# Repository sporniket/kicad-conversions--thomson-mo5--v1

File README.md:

# Conversion of the Thomson MO5 main board into Kicad

> [WARNING] Please read carefully this note before using this project. It contains important facts.

Content

1. What is **Conversion of the Thomson MO5 main board into Kicad**, and when to use it ?
2. What should you know before using **Conversion of the Thomson MO5 main board into Kicad** ?
3. How to use **Conversion of the Thomson MO5 main board into Kicad** ?
4. Known issues
5. Miscellanous

## 1. What is **Conversion of the Thomson MO5 main board into Kicad**, and when to use it ?

**Conversion of the Thomson MO5 main board into Kicad** is a conversion to Kicad EDA of the schematics of a computer released around 1984 known as the "Thomson MO5".

There are two revisions of the motherboard : 

* The first version, with a Motorola gate array, is maintained on the `main` branch.
* The second version, with an EFCIS gate array, is maintained on the `efcis_gate_array` branch.

### Licence

**Conversion of the Thomson MO5 main board into Kicad** is published under the Creative Commons CC0 license. You can find a copy of the licence there : https://creativecommons.org/publicdomain/zero/1.0/legalcode

You can copy, modify, distribute and perform the work, even for commercial purposes, all without asking permission.

**Conversion of the Thomson MO5 main board into Kicad** is distributed in the hope that it will be useful, but WITHOUT ANY WARRANTY; without even the implied warranty of MERCHANTABILITY or FITNESS FOR A PARTICULAR PURPOSE.

### Release notes

#### v1.0.0-rc2

Because I hastily pushed rc1 and saw small edit just after that : one measurement position, refill the copper pours.

Other than that, same as rc1.

#### v1.0.0-rc1

Fixes found by assembling the motherboard :

* Fixed the power supply : pin 1 of I55 to GND, values of R79 and R80 (shematic is also more easy to understand)
* Fixed the reset circuit : value of C01
* Extended the extension port by 2 mm

For documentation :
* [BOM](README--BOM.md)
* Added measurements to the PCB.

#### v1.0.0-beta-2

* Issue #1 -- Small corrections for beta2
  * Schematic -- fixes unit of L01, 'nH' instead of 'mH'
  * wider lateral chamfers for extension connector, set to 1mm along x and y axis
  * prevent a small copper pour of GND inside the extension connector
  * exclude copper pour around internal mounting holes (front layer)
  * tweak the width of the pads of the extension connector, from 2mm to 1.5mm

* Issue #2 -- Small enhancements for beta2
  * Silkscreen -- add text to render REVISION and ISSUE_DATE
  * enlarge vias for modding cartridge port to get E and R/W 
  * Some additionnal fixes of DRC violations
  * Schematic -- D02 value becomes 'BZX46C12'
  * Reset switch -- ad-hoc footprint to combine regular switch with the original reset button footprint

#### v1.0.0-beta-1

The PCB is finished, ready for testing (mechanical, actual assembly) to spot errors.

#### v1.0.0-alpha-1 to v1.0.0-alpha-6

The whole schematics has been captured, need proofreading. A new alpha is produced regularly after some fixes are commited.

## 2. What should you know before using **Conversion of the Thomson MO5 main board into Kicad** ?

**Conversion of the Thomson MO5 main board into Kicad** is made using Kicad 7.

> Do not use **Conversion of the Thomson MO5 main board into Kicad** if this project is not suitable for your project.

## 3. How to use **Conversion of the Thomson MO5 main board into Kicad** ?

### From sources

To get the latest available work, one must clone the git repository.

	git clone --recurse-submodules https://github.com/sporniket/kicad-conversions--thomson-mo5--v1.git

Then, open the project with Kicad 7.

## 4. Known issues
See the [project issues](https://github.com/sporniket/kicad-conversions--thomson-mo5--v1/issues) page.

## 5. Miscellanous

### Report issues
Use the [project issues](https://github.com/sporniket/kicad-conversions--thomson-mo5--v1/issues) page.

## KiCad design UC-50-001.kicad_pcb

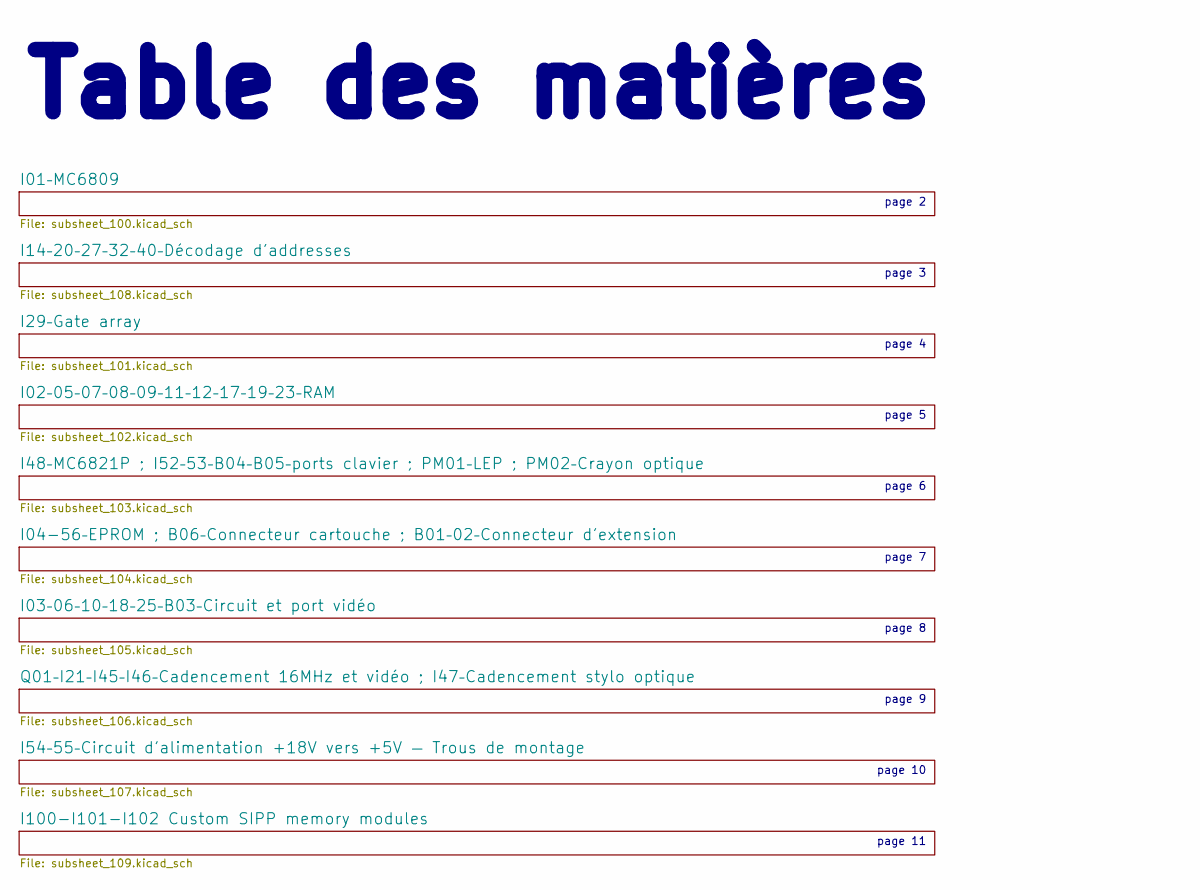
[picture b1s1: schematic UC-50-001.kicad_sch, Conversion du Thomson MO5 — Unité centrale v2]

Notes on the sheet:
page 10
page 2
page 11
page 4
page 6
page 9
page 7
Table des matières
page 5
page 8
page 3

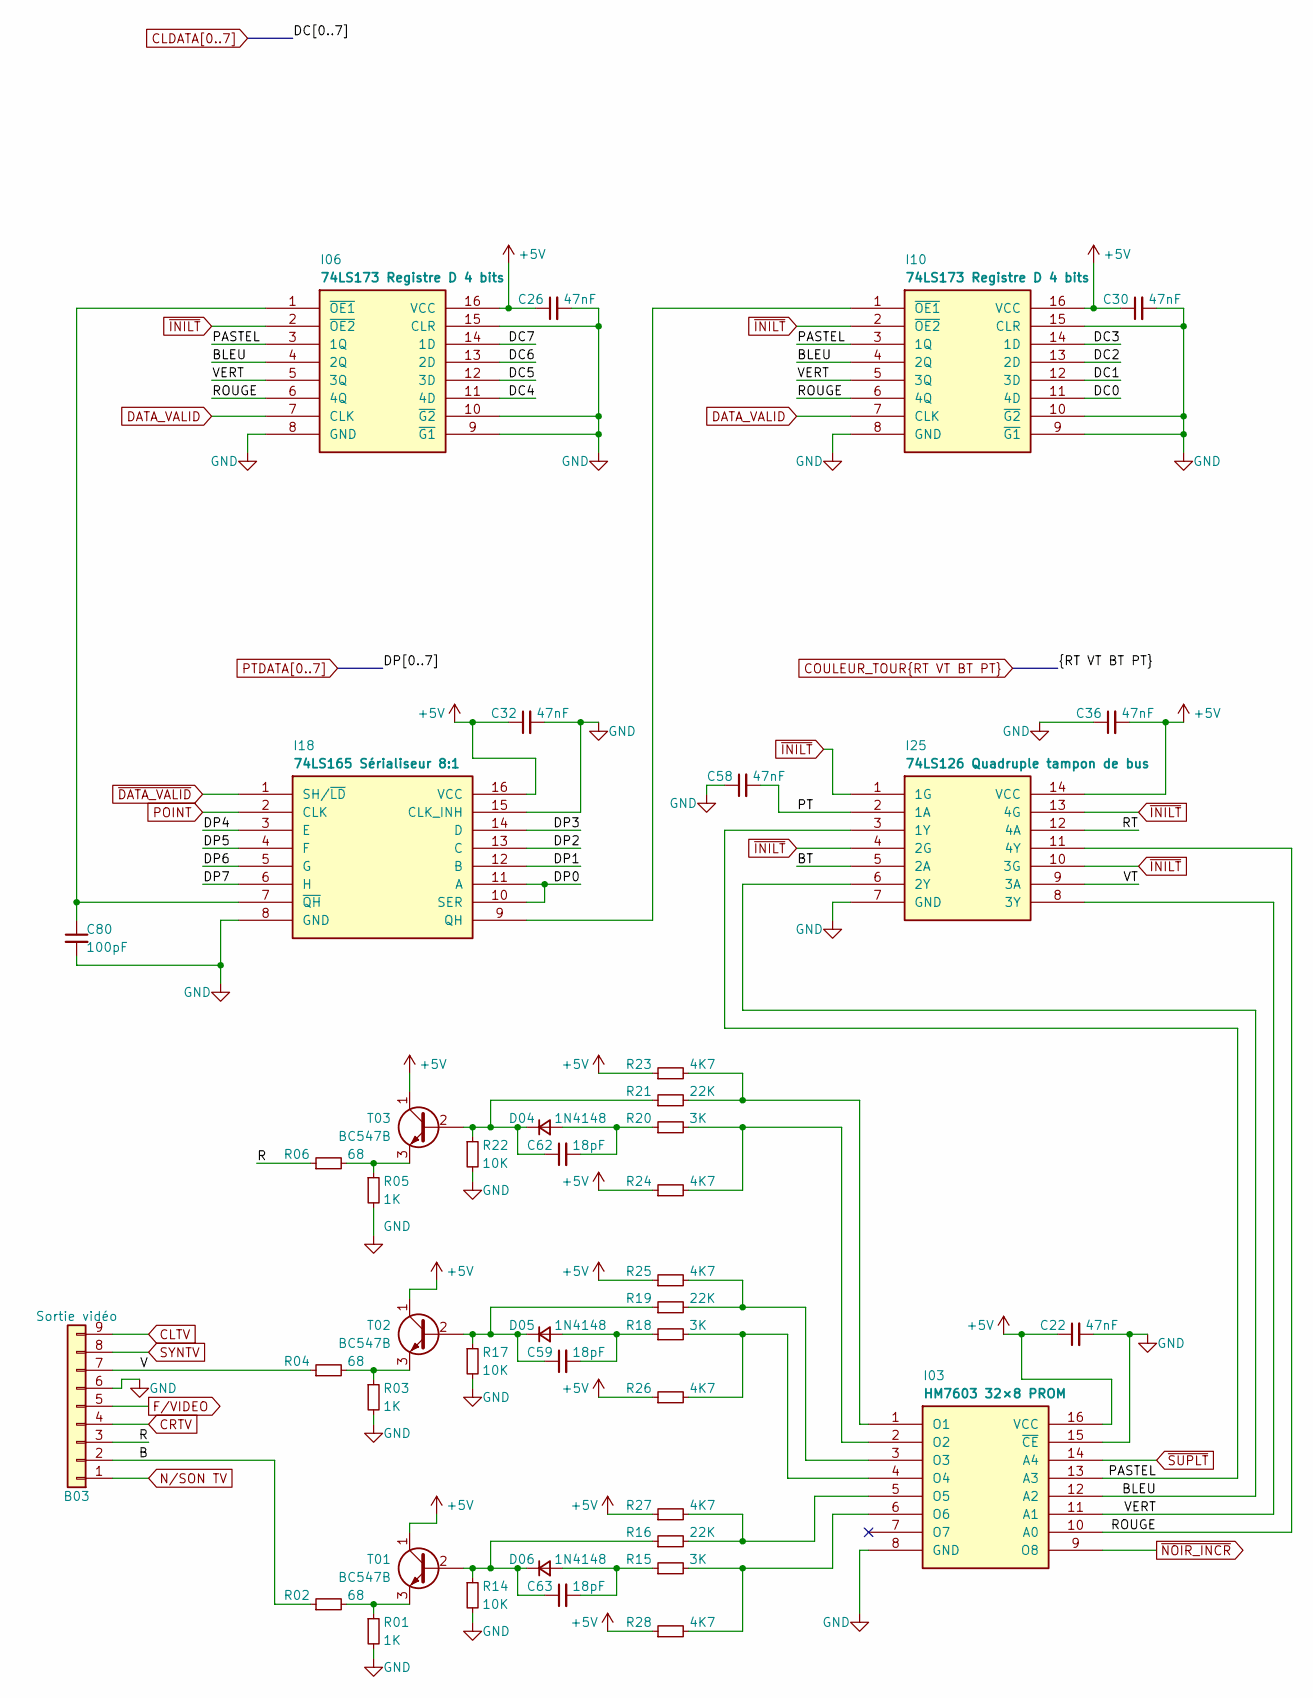
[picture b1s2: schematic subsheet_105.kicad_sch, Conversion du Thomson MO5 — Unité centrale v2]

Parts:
B03: Sortie vidéo; Keyed_MaleReceptacle_1x09_P2.54mm_THT_Vertical
C22, C26, C30, C32, C36, C58: 47nF; Passive_THT_capacitor_mlcc_W2.54mm_L5.08mm
C59, C62, C63: 18pF; Passive_THT_capacitor_mlcc_W2.54mm_L5.08mm
C80: 100pF; Passive_THT_capacitor_mlcc_W2.54mm_L5.08mm
D04, D05, D06: 1N4148; Passive_THT_diode_W2.54mm_L12.70mm
I03: HM7603 32×8 PROM; DIP-16_W7.62mm_LongPads
I06, I10: 74LS173 Registre D 4 bits; DIP-16_W7.62mm_LongPads
I18: 74LS165 Sérialiseur 8:1; DIP-16_W7.62mm_LongPads
I25: 74LS126 Quadruple tampon de bus; DIP-14_W7.62mm_LongPads
R01, R03, R05: 1K; Passive_THT_resistor_EU_W2.54mm_L12.70mm
R02, R04, R06: 68; Passive_THT_resistor_EU_W2.54mm_L12.70mm
R14, R17, R22: 10K; Passive_THT_resistor_EU_W2.54mm_L12.70mm
R15, R18, R20: 3K; Passive_THT_resistor_EU_W2.54mm_L12.70mm
R16, R19, R21: 22K; Passive_THT_resistor_EU_W2.54mm_L12.70mm
R23, R24, R25, R26, R27, R28: 4K7; Passive_THT_resistor_EU_W2.54mm_L12.70mm
T01, T02, T03: BC547B; TO-92_Inline_Wide

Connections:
+5V: C22.1, C26.1, C30.1, C32.1, C36.2, I03.16 (VCC), I06.16 (VCC), I10.16 (VCC), I18.16 (VCC), I25.14 (VCC), R23.1, R24.1, R25.1, R26.1, R27.1, R28.1, T01.1 (C), T02.1 (C), T03.1 (C); also elsewhere on the board
/I03–06–10–18–25–B03–Circuit et port vidéo /B: B03.2, R02.1
/I03–06–10–18–25–B03–Circuit et port vidéo /BLEU: I03.12 (A2), I06.4 (2Q), I10.4 (2Q), I25.6 (2Y)
/I03–06–10–18–25–B03–Circuit et port vidéo /PASTEL: I03.13 (A3), I06.3 (1Q), I10.3 (1Q), I25.3 (1Y)
/I03–06–10–18–25–B03–Circuit et port vidéo /R: B03.3, R06.1
/I03–06–10–18–25–B03–Circuit et port vidéo /ROUGE: I03.10 (A0), I06.6 (4Q), I10.6 (4Q), I25.11 (4Y)
/I03–06–10–18–25–B03–Circuit et port vidéo /V: B03.7, R04.1
/I03–06–10–18–25–B03–Circuit et port vidéo /VERT: I03.11 (A1), I06.5 (3Q), I10.5 (3Q), I25.8 (3Y)
CLDATA0: I10.11 (4D); also elsewhere on the board
CLDATA1: I10.12 (3D); also elsewhere on the board
CLDATA2: I10.13 (2D); also elsewhere on the board
CLDATA3: I10.14 (1D); also elsewhere on the board
CLDATA4: I06.11 (4D); also elsewhere on the board
CLDATA5: I06.12 (3D); also elsewhere on the board
CLDATA6: I06.13 (2D); also elsewhere on the board
CLDATA7: I06.14 (1D); also elsewhere on the board
CLTV: B03.9; also elsewhere on the board
COULEUR_TOUR.BT: I25.5 (2A); also elsewhere on the board
COULEUR_TOUR.PT: C58.2, I25.2 (1A); also elsewhere on the board
COULEUR_TOUR.RT: I25.12 (4A); also elsewhere on the board
COULEUR_TOUR.VT: I25.9 (3A); also elsewhere on the board
CRTV: B03.4; also elsewhere on the board
DATA_VALID: I06.7 (CLK), I10.7 (CLK); also elsewhere on the board
F/VIDEO: B03.5; also elsewhere on the board
GND: B03.6, C22.2, C26.2, C30.2, C32.2, C36.1, C58.1, C80.2, I03.8 (GND), I03.15 (~CE), I06.8 (GND), I06.9 (~G1), I06.10 (~G2), I06.15 (CLR), I10.8 (GND), I10.9 (~G1), I10.10 (~G2), I10.15 (CLR), I18.8 (GND), I18.15 (CLK_INH), I25.7 (GND), R01.2, R03.2, R05.2, R14.2, R17.2, R22.2; also elsewhere on the board
unnamed: C62.2, D04.2 (A), R20.1
unnamed: C62.1, D04.1 (K), R21.1, R22.1, T03.2 (B)
unnamed: C59.2, D05.2 (A), R18.1
unnamed: C59.1, D05.1 (K), R17.1, R19.1, T02.2 (B)
unnamed: C63.2, D06.2 (A), R15.1
unnamed: C63.1, D06.1 (K), R14.1, R16.1, T01.2 (B)
unnamed: I03.1 (O1), R21.2, R23.2
unnamed: I03.2 (O2), R20.2, R24.2
unnamed: I03.3 (O3), R19.2, R25.2
unnamed: I03.4 (O4), R18.2, R26.2
unnamed: I03.5 (O5), R16.2, R27.2
unnamed: I03.6 (O6), R15.2, R28.2
unnamed: C80.1, I06.1 (~OE1), I18.7 (~QH)
unnamed: I10.1 (~OE1), I18.9 (QH)
unnamed: R01.1, R02.2, T01.3 (E)
unnamed: R03.1, R04.2, T02.3 (E)
unnamed: R05.1, R06.2, T03.3 (E)
N/SON TV: B03.1; also elsewhere on the board
POINT: I18.2 (CLK); also elsewhere on the board
PTDATA0: I18.10 (SER), I18.11 (A); also elsewhere on the board
PTDATA1: I18.12 (B); also elsewhere on the board
PTDATA2: I18.13 (C); also elsewhere on the board
PTDATA3: I18.14 (D); also elsewhere on the board
PTDATA4: I18.3 (E); also elsewhere on the board
PTDATA5: I18.4 (F); also elsewhere on the board
PTDATA6: I18.5 (G); also elsewhere on the board
PTDATA7: I18.6 (H); also elsewhere on the board
SYNTV: B03.8; also elsewhere on the board
~DATA_VALID: I18.1 (SH/~LD); also elsewhere on the board
~INILT: I06.2 (~OE2), I10.2 (~OE2), I25.1 (1G), I25.4 (2G), I25.10 (3G), I25.13 (4G); also elsewhere on the board
~NOIR_INCR: I03.9 (O8); also elsewhere on the board
~SUPLT: I03.14 (A4); also elsewhere on the board

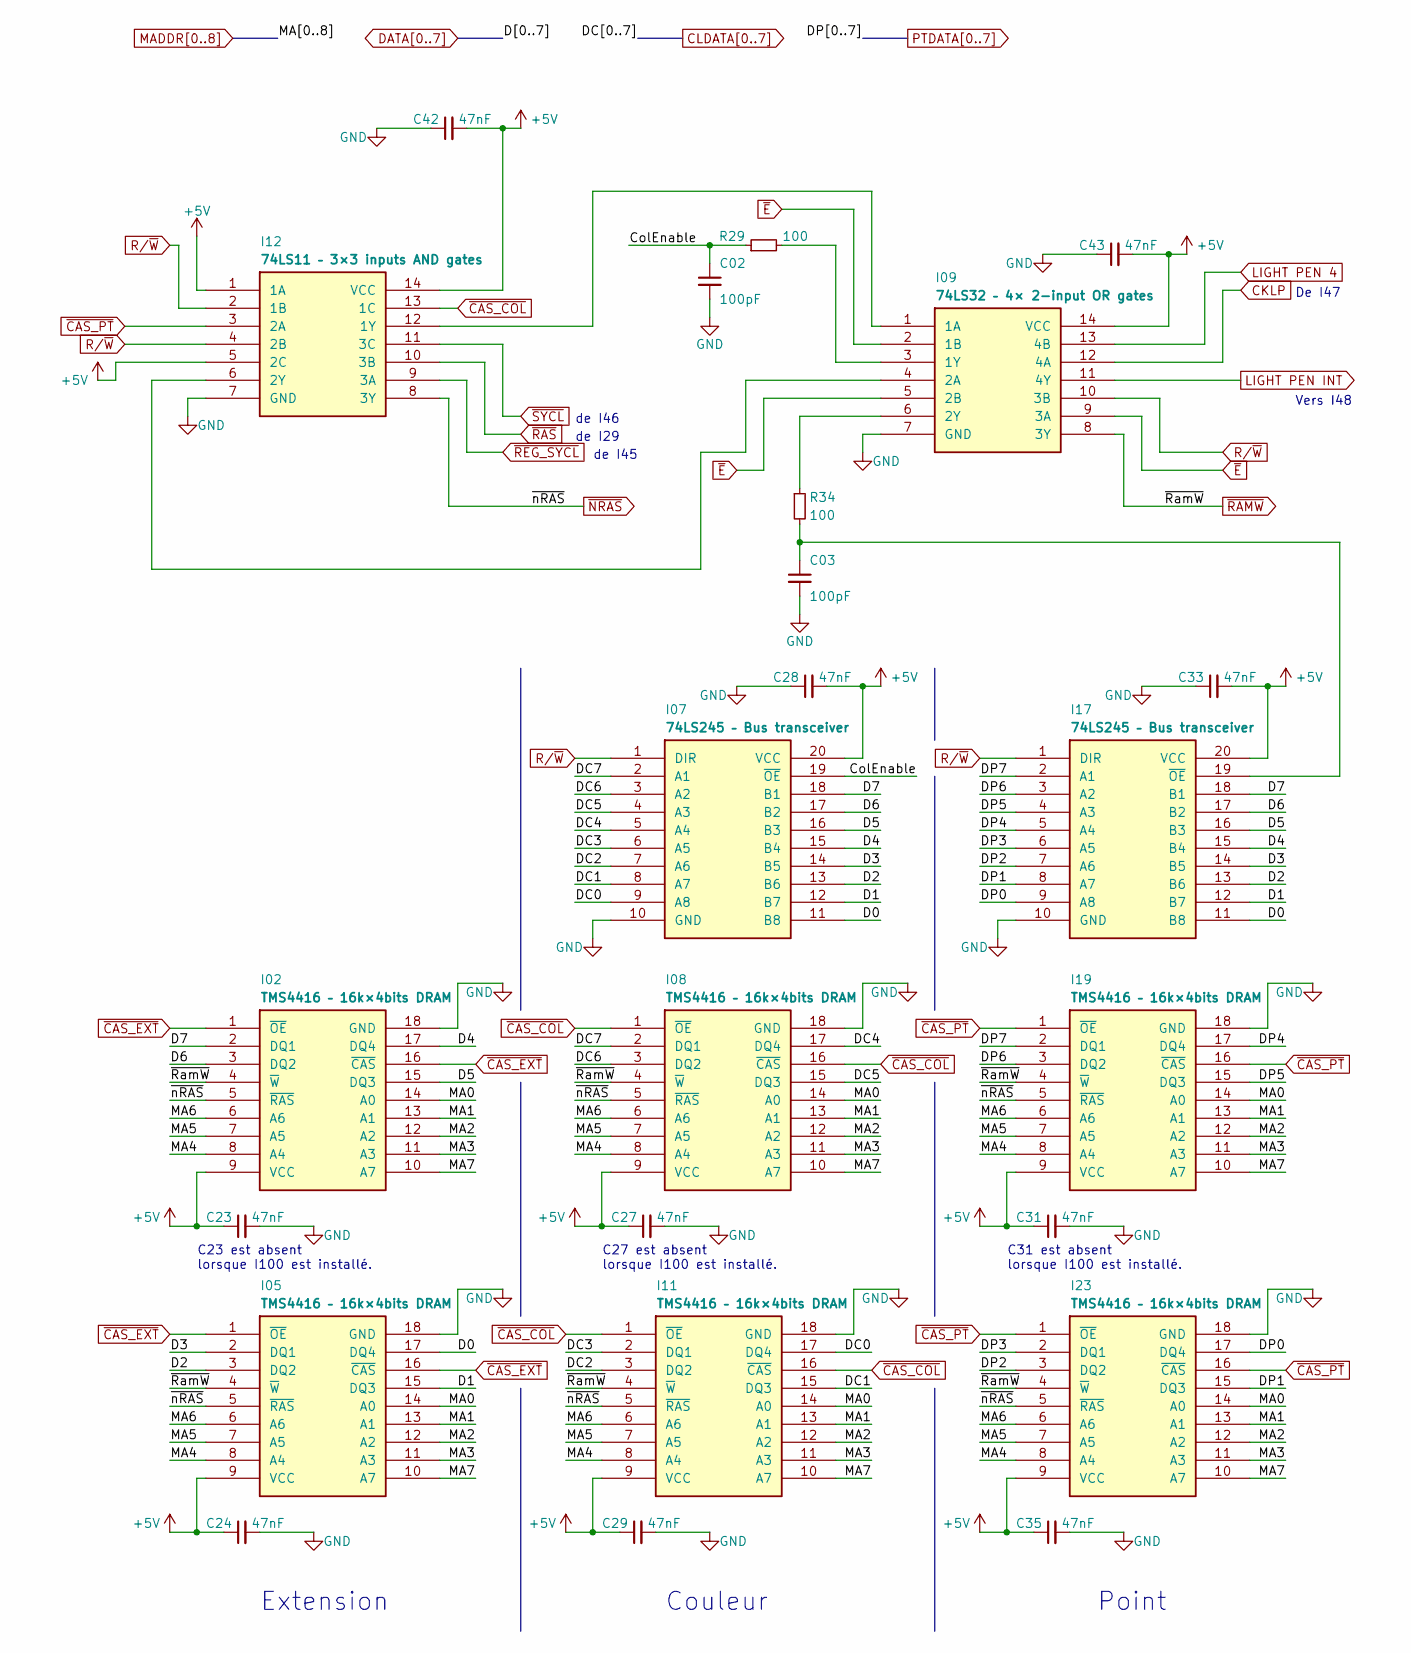
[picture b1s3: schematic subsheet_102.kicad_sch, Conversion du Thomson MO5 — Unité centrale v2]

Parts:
C02, C03: 100pF; Passive_THT_capacitor_mlcc_W2.54mm_L5.08mm
C23, C24, C27, C28, C29, C31, C33, C35, C42, C43: 47nF; Passive_THT_capacitor_mlcc_W2.54mm_L5.08mm
I02, I05, I08, I11, I19, I23: TMS4416 – 16k×4bits DRAM; DIP-18_W7.62mm_LongPads
I07, I17: 74LS245 – Bus transceiver; DIP-20_W7.62mm_LongPads
I09: 74LS32 – 4× 2-input OR gates; DIP-14_W7.62mm_LongPads
I12: 74LS11 – 3×3 inputs AND gates; DIP-14_W7.62mm_LongPads
R29, R34: 100; Passive_THT_resistor_EU_W2.54mm_L12.70mm

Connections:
+5V: C23.1, C24.1, C27.1, C28.2, C29.1, C31.1, C33.2, C35.1, C42.2, C43.2, I02.9 (VCC), I05.9 (VCC), I07.20 (VCC), I08.9 (VCC), I09.14 (VCC), I11.9 (VCC), I12.1 (1A), I12.5 (2C), I12.14 (VCC), I17.20 (VCC), I19.9 (VCC), I23.9 (VCC); also elsewhere on the board
/I02–05–07–08–09–11–12–17–19–23–RAM/ColEnable: C02.1, I07.19 (~OE), R29.1
CKLP: I09.12 (4A); also elsewhere on the board
CLDATA0: I07.9 (A8), I11.17 (DQ4); also elsewhere on the board
CLDATA1: I07.8 (A7), I11.15 (DQ3); also elsewhere on the board
CLDATA2: I07.7 (A6), I11.3 (DQ2); also elsewhere on the board
CLDATA3: I07.6 (A5), I11.2 (DQ1); also elsewhere on the board
CLDATA4: I07.5 (A4), I08.17 (DQ4); also elsewhere on the board
CLDATA5: I07.4 (A3), I08.15 (DQ3); also elsewhere on the board
CLDATA6: I07.3 (A2), I08.3 (DQ2); also elsewhere on the board
CLDATA7: I07.2 (A1), I08.2 (DQ1); also elsewhere on the board
DATA0: I05.17 (DQ4), I07.11 (B8), I17.11 (B8); also elsewhere on the board
DATA1: I05.15 (DQ3), I07.12 (B7), I17.12 (B7); also elsewhere on the board
DATA2: I05.3 (DQ2), I07.13 (B6), I17.13 (B6); also elsewhere on the board
DATA3: I05.2 (DQ1), I07.14 (B5), I17.14 (B5); also elsewhere on the board
DATA4: I02.17 (DQ4), I07.15 (B4), I17.15 (B4); also elsewhere on the board
DATA5: I02.15 (DQ3), I07.16 (B3), I17.16 (B3); also elsewhere on the board
DATA6: I02.3 (DQ2), I07.17 (B2), I17.17 (B2); also elsewhere on the board
DATA7: I02.2 (DQ1), I07.18 (B1), I17.18 (B1); also elsewhere on the board
GND: C02.2, C03.2, C23.2, C24.2, C27.2, C28.1, C29.2, C31.2, C33.1, C35.2, C42.1, C43.1, I02.18 (GND), I05.18 (GND), I07.10 (GND), I08.18 (GND), I09.7 (GND), I11.18 (GND), I12.7 (GND), I17.10 (GND), I19.18 (GND), I23.18 (GND); also elsewhere on the board
LIGHT PEN 4: I09.13 (4B); also elsewhere on the board
LIGHT PEN INT: I09.11 (4Y); also elsewhere on the board
MADDR0: I02.14 (A0), I05.14 (A0), I08.14 (A0), I11.14 (A0), I19.14 (A0), I23.14 (A0); also elsewhere on the board
MADDR1: I02.13 (A1), I05.13 (A1), I08.13 (A1), I11.13 (A1), I19.13 (A1), I23.13 (A1); also elsewhere on the board
MADDR2: I02.12 (A2), I05.12 (A2), I08.12 (A2), I11.12 (A2), I19.12 (A2), I23.12 (A2); also elsewhere on the board
MADDR3: I02.11 (A3), I05.11 (A3), I08.11 (A3), I11.11 (A3), I19.11 (A3), I23.11 (A3); also elsewhere on the board
MADDR4: I02.8 (A4), I05.8 (A4), I08.8 (A4), I11.8 (A4), I19.8 (A4), I23.8 (A4); also elsewhere on the board
MADDR5: I02.7 (A5), I05.7 (A5), I08.7 (A5), I11.7 (A5), I19.7 (A5), I23.7 (A5); also elsewhere on the board
MADDR6: I02.6 (A6), I05.6 (A6), I08.6 (A6), I11.6 (A6), I19.6 (A6), I23.6 (A6); also elsewhere on the board
MADDR7: I02.10 (A7), I05.10 (A7), I08.10 (A7), I11.10 (A7), I19.10 (A7), I23.10 (A7); also elsewhere on the board
unnamed: I09.1 (1A), I12.12 (1Y)
unnamed: I09.3 (1Y), R29.2
unnamed: I09.4 (2A), I12.6 (2Y)
unnamed: I09.6 (2Y), R34.1
unnamed: C03.1, I17.19 (~OE), R34.2
PTDATA0: I17.9 (A8), I23.17 (DQ4); also elsewhere on the board
PTDATA1: I17.8 (A7), I23.15 (DQ3); also elsewhere on the board
PTDATA2: I17.7 (A6), I23.3 (DQ2); also elsewhere on the board
PTDATA3: I17.6 (A5), I23.2 (DQ1); also elsewhere on the board
PTDATA4: I17.5 (A4), I19.17 (DQ4); also elsewhere on the board
PTDATA5: I17.4 (A3), I19.15 (DQ3); also elsewhere on the board
PTDATA6: I17.3 (A2), I19.3 (DQ2); also elsewhere on the board
PTDATA7: I17.2 (A1), I19.2 (DQ1); also elsewhere on the board
R/~W: I07.1 (DIR), I09.10 (3B), I12.2 (1B), I12.4 (2B), I17.1 (DIR); also elsewhere on the board
~CAS_COL: I08.1 (~OE), I08.16 (~CAS), I11.1 (~OE), I11.16 (~CAS), I12.13 (1C); also elsewhere on the board
~CAS_EXT: I02.1 (~OE), I02.16 (~CAS), I05.1 (~OE), I05.16 (~CAS); also elsewhere on the board
~CAS_PT: I12.3 (2A), I19.1 (~OE), I19.16 (~CAS), I23.1 (~OE), I23.16 (~CAS); also elsewhere on the board
~E: I09.2 (1B), I09.5 (2B), I09.9 (3A); also elsewhere on the board
~NRAS: I02.5 (~RAS), I05.5 (~RAS), I08.5 (~RAS), I11.5 (~RAS), I12.8 (3Y), I19.5 (~RAS), I23.5 (~RAS); also elsewhere on the board
~RAMW: I02.4 (~W), I05.4 (~W), I08.4 (~W), I09.8 (3Y), I11.4 (~W), I19.4 (~W), I23.4 (~W); also elsewhere on the board
~RAS: I12.10 (3B); also elsewhere on the board
~REG_SYCL: I12.9 (3A); also elsewhere on the board
~SYCL: I12.11 (3C); also elsewhere on the board

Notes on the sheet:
C31 est absent lorsque I100 est installé.
de I29
Extension
Vers I48
C27 est absent lorsque I100 est installé.
de I45
C23 est absent lorsque I100 est installé.
De I47
Couleur
de I46
Point

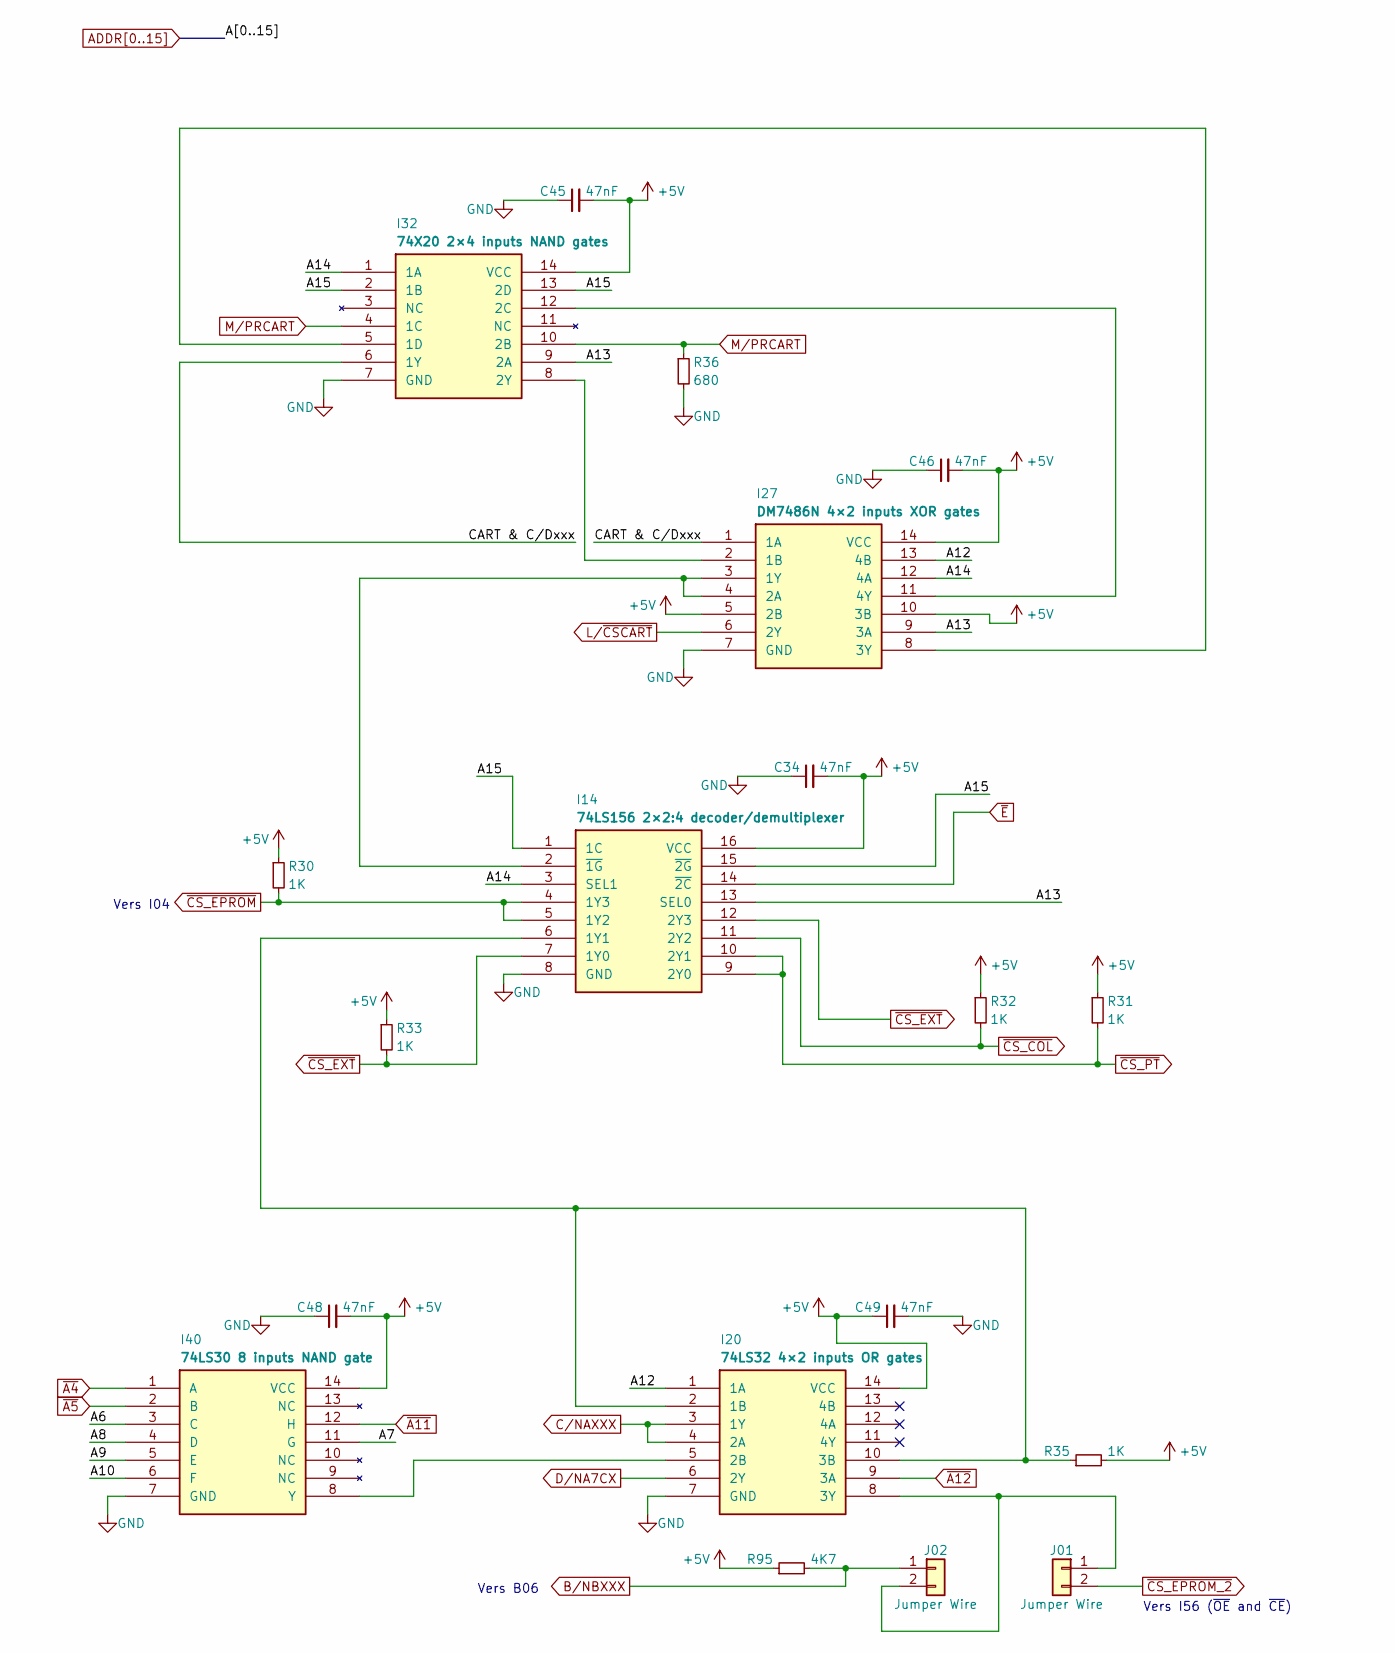
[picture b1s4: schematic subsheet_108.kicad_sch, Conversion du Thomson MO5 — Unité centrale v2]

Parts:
C34, C45, C46, C48, C49: 47nF; Passive_THT_capacitor_mlcc_W2.54mm_L5.08mm
I14: 74LS156 2×2:4 decoder/demultiplexer; DIP-16_W7.62mm_LongPads
I20: 74LS32 4×2 inputs OR gates; DIP-14_W7.62mm_LongPads
I27: DM7486N 4×2 inputs XOR gates; DIP-14_W7.62mm_LongPads
I32: 74X20 2×4 inputs NAND gates; DIP-14_W7.62mm_LongPads
I40: 74LS30 8 inputs NAND gate; DIP-14_W7.62mm_LongPads
J01, J02: Jumper Wire; Passive_THT_jumper_wire_W2.54mm_L10.16mm
R30, R31, R32, R33, R35: 1K; Passive_THT_resistor_EU_W2.54mm_L12.70mm
R36: 680; Passive_THT_resistor_EU_W2.54mm_L12.70mm
R95: 4K7; Passive_THT_resistor_EU_W2.54mm_L12.70mm

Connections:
+5V: C34.2, C45.2, C46.2, C48.2, C49.1, I14.16 (VCC), I20.14 (VCC), I27.5 (2B), I27.10 (3B), I27.14 (VCC), I32.14 (VCC), I40.14 (VCC), R30.1, R31.1, R32.1, R33.1, R35.2, R95.1; also elsewhere on the board
/I14–20–27–32–40–Décodage d'addresses/CART & C/Dxxx: I27.1 (1A), I32.6 (1Y)
ADDR6: I40.3 (C); also elsewhere on the board
ADDR7: I40.11 (G); also elsewhere on the board
ADDR8: I40.4 (D); also elsewhere on the board
ADDR9: I40.5 (E); also elsewhere on the board
ADDR10: I40.6 (F); also elsewhere on the board
ADDR12: I20.1 (1A), I27.13 (4B); also elsewhere on the board
ADDR13: I14.13 (SEL0), I27.9 (3A), I32.9 (2A); also elsewhere on the board
ADDR14: I14.3 (SEL1), I27.12 (4A), I32.1 (1A); also elsewhere on the board
ADDR15: I14.1 (1C), I14.15 (~2G), I32.2 (1B), I32.13 (2D); also elsewhere on the board
B/NBXXX: J02.1, R95.2; also elsewhere on the board
C/NAXXX: I20.3 (1Y), I20.4 (2A); also elsewhere on the board
D/NA7CX: I20.6 (2Y); also elsewhere on the board
GND: C34.1, C45.1, C46.1, C48.1, C49.2, I14.8 (GND), I20.7 (GND), I27.7 (GND), I32.7 (GND), I40.7 (GND), R36.2; also elsewhere on the board
L/~CSCART: I27.6 (2Y); also elsewhere on the board
M/PRCART: I32.4 (1C), I32.10 (2B), R36.1; also elsewhere on the board
unnamed: I14.6 (1Y1), I20.2 (1B), I20.10 (3B), R35.1
unnamed: I14.2 (~1G), I27.3 (1Y), I27.4 (2A)
unnamed: I20.5 (2B), I40.8 (Y)
unnamed: I20.8 (3Y), J01.1, J02.2
unnamed: I27.2 (1B), I32.8 (2Y)
unnamed: I27.8 (3Y), I32.5 (1D)
unnamed: I27.11 (4Y), I32.12 (2C)
~A4: I40.1 (A); also elsewhere on the board
~A5: I40.2 (B); also elsewhere on the board
~A11: I40.12 (H); also elsewhere on the board
~A12: I20.9 (3A); also elsewhere on the board
~CS_COL: I14.11 (2Y2), R32.2; also elsewhere on the board
~CS_EPROM_2: J01.2; also elsewhere on the board
~CS_EPROM: I14.4 (1Y3), I14.5 (1Y2), R30.2; also elsewhere on the board
~CS_EXT: I14.7 (1Y0), I14.12 (2Y3), R33.2; also elsewhere on the board
~CS_PT: I14.9 (2Y0), I14.10 (2Y1), R31.2; also elsewhere on the board
~E: I14.14 (~2C); also elsewhere on the board

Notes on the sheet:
Vers I56 (~{OE} and ~{CE})
Vers B06
Vers I04

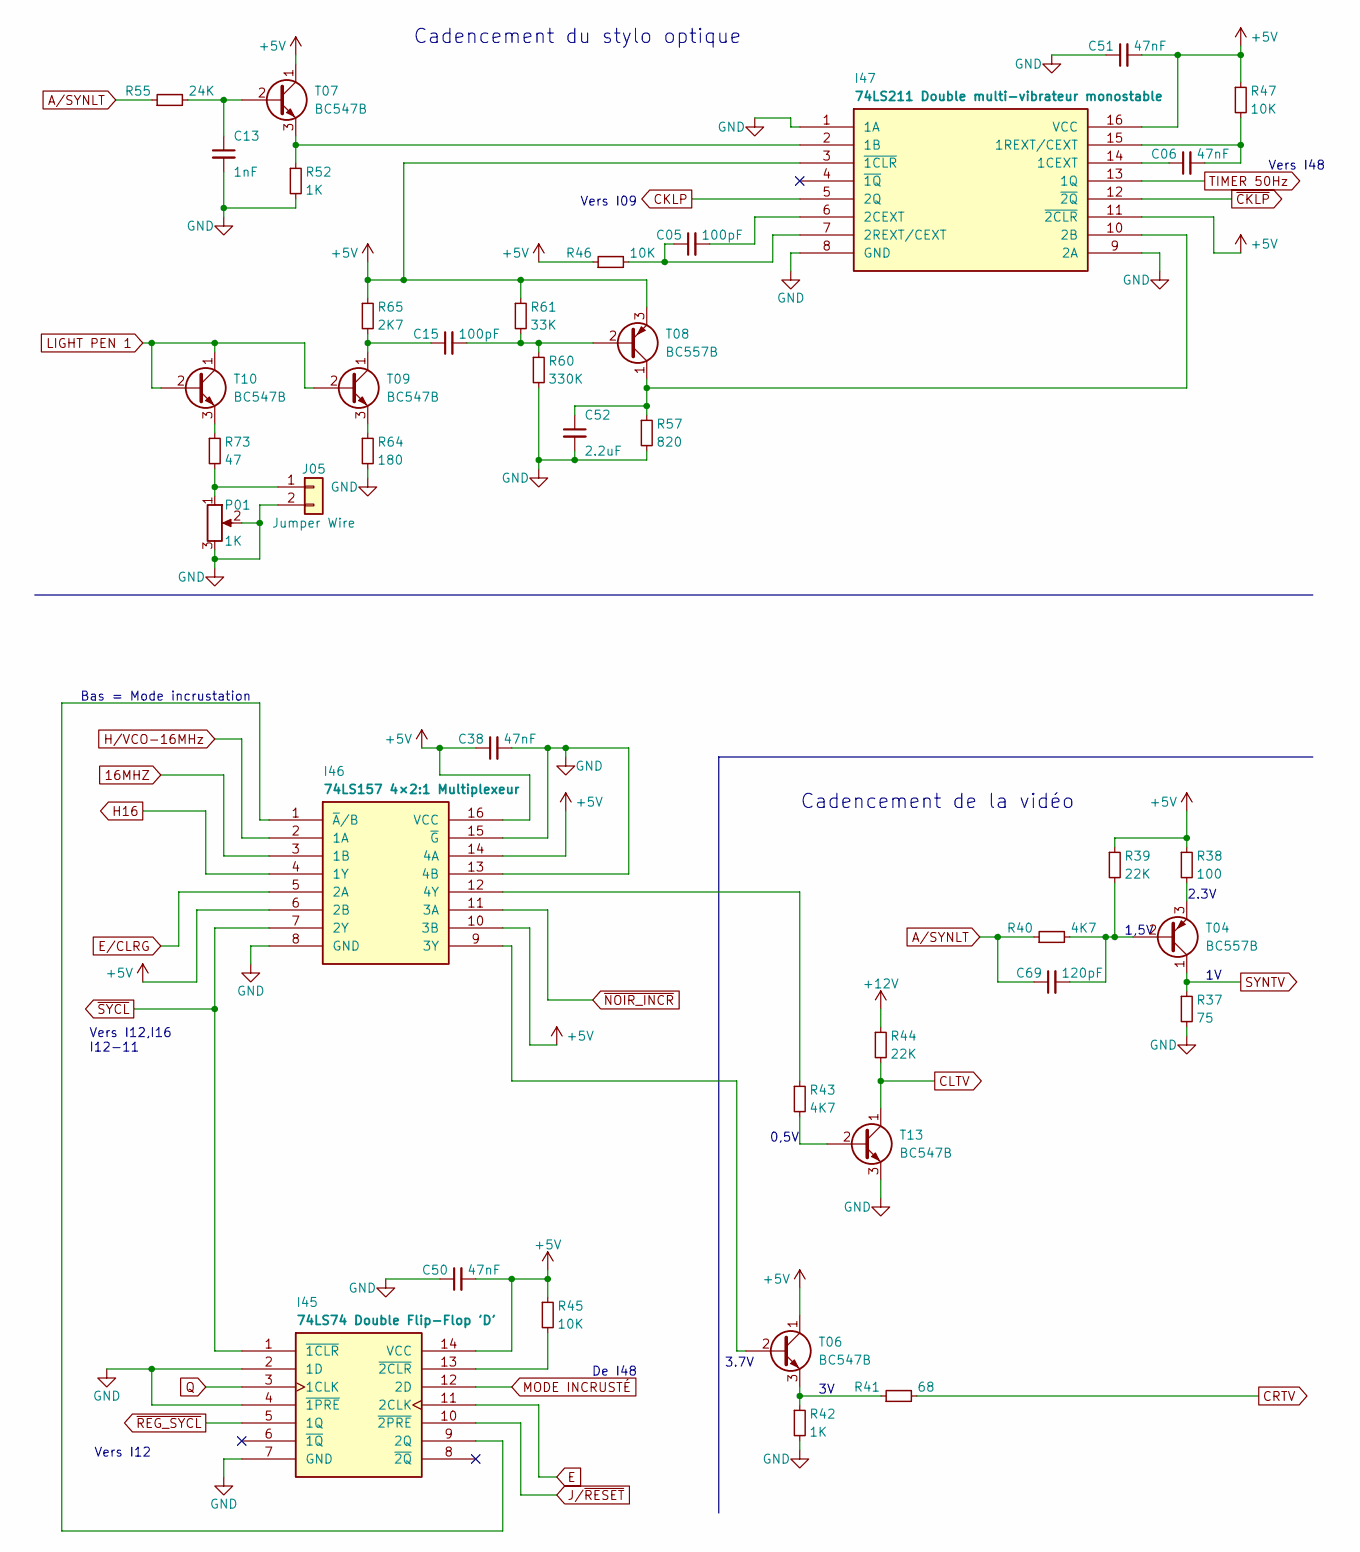
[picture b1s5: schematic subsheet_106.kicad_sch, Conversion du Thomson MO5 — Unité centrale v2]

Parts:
C05, C15: 100pF; Passive_THT_capacitor_mlcc_W2.54mm_L5.08mm
C06, C38, C50, C51: 47nF; Passive_THT_capacitor_mlcc_W2.54mm_L5.08mm
C13: 1nF; Passive_THT_capacitor_mlcc_W2.54mm_L5.08mm
C52: 2.2uF; Passive_THT_capacitor_mlcc_W2.54mm_L5.08mm
C69: 120pF; Passive_THT_capacitor_mlcc_W2.54mm_L5.08mm
I45: 74LS74 Double Flip-Flop 'D'; DIP-14_W7.62mm_LongPads
I46: 74LS157 4×2:1 Multiplexeur; DIP-16_W7.62mm_LongPads
I47: 74LS211 Double multi-vibrateur monostable; DIP-16_W7.62mm_LongPads
J05: Jumper Wire; Passive_THT_jumper_wire_W2.54mm_L12.70mm
P01: 1K; Potentiometer_ACP_CA9-V10_Vertical_Hole
R37: 75; Passive_THT_resistor_EU_W2.54mm_L12.70mm
R38: 100; Passive_THT_resistor_EU_W2.54mm_L12.70mm
R39, R44: 22K; Passive_THT_resistor_EU_W2.54mm_L12.70mm
R40, R43: 4K7; Passive_THT_resistor_EU_W2.54mm_L12.70mm
R41: 68; Passive_THT_resistor_EU_W2.54mm_L12.70mm
R42, R52: 1K; Passive_THT_resistor_EU_W2.54mm_L12.70mm
R45, R46, R47: 10K; Passive_THT_resistor_EU_W2.54mm_L12.70mm
R55: 24K; Passive_THT_resistor_EU_W2.54mm_L12.70mm
R57: 820; Passive_THT_resistor_EU_W2.54mm_L12.70mm
R60: 330K; Passive_THT_resistor_EU_W2.54mm_L12.70mm
R61: 33K; Passive_THT_resistor_EU_W2.54mm_L12.70mm
R64: 180; Passive_THT_resistor_EU_W2.54mm_L12.70mm
R65: 2K7; Passive_THT_resistor_EU_W2.54mm_L12.70mm
R73: 47; Passive_THT_resistor_EU_W2.54mm_L12.70mm
T04, T08: BC557B; TO-92_Inline_Wide
T06, T07, T09, T10, T13: BC547B; TO-92_Inline_Wide

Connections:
16MHZ: I46.3 (1B); also elsewhere on the board
+5V: C38.1, C50.2, C51.2, I45.14 (VCC), I46.6 (2B), I46.10 (3B), I46.14 (4A), I46.16 (VCC), I47.3 (~1CLR), I47.11 (~2CLR), I47.16 (VCC), R38.1, R39.1, R45.1, R46.1, R47.1, R61.1, R65.1, T06.1 (C), T07.1 (C), T08.3 (E); also elsewhere on the board
+12V: R44.1; also elsewhere on the board
A/SYNLT: C69.1, R40.1, R55.1; also elsewhere on the board
CKLP: I47.5 (2Q); also elsewhere on the board
CLTV: R44.2, T13.1 (C); also elsewhere on the board
CRTV: R41.2; also elsewhere on the board
E: I45.11 (2CLK); also elsewhere on the board
E/CLRG: I46.5 (2A); also elsewhere on the board
GND: C13.2, C38.2, C50.1, C51.1, C52.2, I45.2 (1D), I45.4 (~1PRE), I45.7 (GND), I46.8 (GND), I46.13 (4B), I46.15 (~G), I47.1 (1A), I47.8 (GND), I47.9 (2A), J05.2, P01.2, P01.3, R37.2, R42.2, R52.2, R57.2, R60.2, R64.2, T13.3 (E); also elsewhere on the board
H16: I46.4 (1Y); also elsewhere on the board
H/VCO-16MHz: I46.2 (1A); also elsewhere on the board
J/~RESET: I45.10 (~2PRE); also elsewhere on the board
LIGHT PEN 1: T09.2 (B), T10.1 (C), T10.2 (B); also elsewhere on the board
MODE INCRUSTÉ: I45.12 (2D); also elsewhere on the board
unnamed: I45.9 (2Q), I46.1 (~A/B)
unnamed: I45.13 (~2CLR), R45.2
unnamed: I46.9 (3Y), T06.2 (B)
unnamed: I46.12 (4Y), R43.1
unnamed: I47.2 (1B), R52.1, T07.3 (E)
unnamed: C06.1, I47.14 (1CEXT)
unnamed: C06.2, I47.15 (1REXT/CEXT), R47.2
unnamed: C52.1, I47.10 (2B), R57.1, T08.1 (C)
unnamed: C05.2, I47.6 (2CEXT)
unnamed: C05.1, I47.7 (2REXT/CEXT), R46.2
unnamed: J05.1, P01.1, R73.2
unnamed: C69.2, R39.2, R40.2, T04.2 (B)
unnamed: R38.2, T04.3 (E)
unnamed: R41.1, R42.1, T06.3 (E)
unnamed: C13.1, R55.2, T07.2 (B)
unnamed: C15.2, R60.1, R61.2, T08.2 (B)
unnamed: C15.1, R65.2, T09.1 (C)
unnamed: R64.1, T09.3 (E)
unnamed: R73.1, T10.3 (E)
unnamed: R43.2, T13.2 (B)
Q: I45.3 (1CLK); also elsewhere on the board
SYNTV: R37.1, T04.1 (C); also elsewhere on the board
TIMER 50Hz: I47.13 (1Q); also elsewhere on the board
~CKLP: I47.12 (~2Q); also elsewhere on the board
~NOIR_INCR: I46.11 (3A); also elsewhere on the board
~REG_SYCL: I45.5 (1Q); also elsewhere on the board
~SYCL: I45.1 (~1CLR), I46.7 (2Y); also elsewhere on the board

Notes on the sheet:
3.7V
Cadencement de la vidéo
Vers I09
2.3V
0,5V
De I48
1,5V
Vers I48
Cadencement du stylo optique
Vers I12,I16 I12-11
Vers I12
Bas = Mode incrustation
